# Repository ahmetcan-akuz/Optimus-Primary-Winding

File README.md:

# Optimus-Primary-Winding
This is the EE 464 Hardware Project Repository of Optimus Primary Winding

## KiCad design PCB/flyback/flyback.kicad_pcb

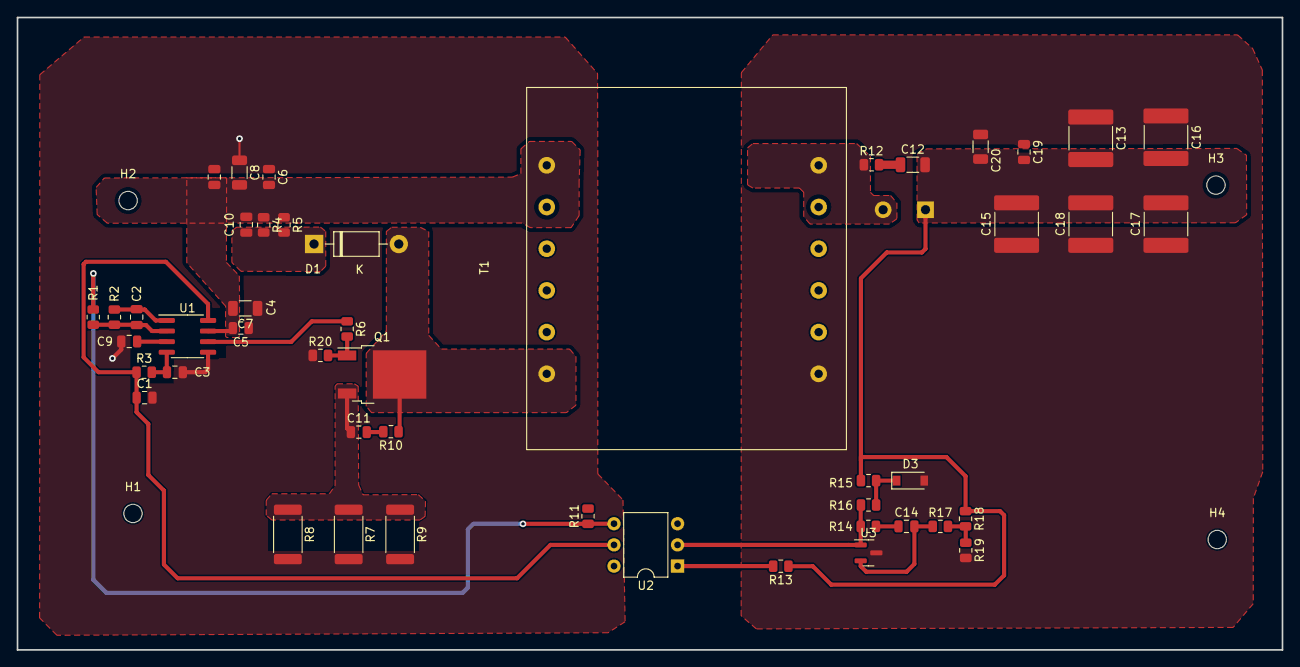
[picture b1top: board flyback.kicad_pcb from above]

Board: 2 copper layers, 151.7 x 75.8 mm, 52 parts (1 on the bottom side), 24 nets.

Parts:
C1, C4: 1u; C_0805_2012Metric
C2: 100p; C_0805_2012Metric
C3: 2.2n; C_0805_2012Metric
C5, C6, C19: 100n; C_0805_2012Metric
C7, C8, C20: 10n; C_1206_3216Metric
C9: 0.47n; C_0805_2012Metric
C10: 220n; C_0805_2012Metric
C11: 4.7n; C_0805_2012Metric
C12: 470p; C_1206_3216Metric
C13, C15, C16, C17: 10u; C_2220_5650Metric
C14: 1n; C_0805_2012Metric
C18: 4.7u; C_2220_5650Metric
D1: 1N4002; D_DO-41_SOD81_P10.16mm_Horizontal
D2: MBR10150; TO-220-2_Vertical
D3: MMSZ4713; D_SOD-123
H1, H2, H3, H4: MountingHole_Pad; MountingHole_2.2mm_M2
Q1: IRFR3410TRLPBF; TO-252-2
R1: 4.7k; R_0805_2012Metric
R2, R13, R15: 22k; R_0805_2012Metric
R3: 12k; R_0805_2012Metric
R4, R5, R16: 1k; R_0805_2012Metric
R6: 10; R_0805_2012Metric
R7, R8, R9: 150m; R_2512_6332Metric
R10: 47; R_0805_2012Metric
R11, R17, R19, R20: 10k; R_0805_2012Metric
R12: 100; R_0805_2012Metric
R14: 820k; R_0805_2012Metric
R18: 182k; R_0805_2012Metric
T1: Transformer_1P_1S; Transformer_37x44
U1: UC3843_SOIC8; SOIC-8_3.9x4.9mm_P1.27mm
U2: 4N25; DIP-6_W7.62mm
U3: TL431DBZ; SOT-23

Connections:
/Vfb: R1.1, R11.1, U2.4
/Vin: C4.2, C5.2, C6.2, C7.2, C8.2, C10.1, R4.1, R5.1, T1.6 (AA), U1.7 (VCC)
/Vout: C12.2, C13.2, C15.2, C16.2, C17.2, C18.2, C19.2, C20.2, D2.1 (K), R13.1, R15.1, R18.1
/Vref: C1.1, R3.1, U1.8 (VREF), U2.5
GND1: C1.2, C3.2, C4.1, C5.1, C6.1, C7.1, C8.1, C9.1, R7.2, R8.2, R9.2, R20.1, U1.5 (GND)
GND2: C13.1, C15.1, C16.1, C17.1, C18.1, C19.1, C20.1, D3.2 (A), R19.2, T1.12 (SA), U3.3 (A)
unnamed: C2.1, R1.2, R2.1, U1.2 (FB)
unnamed: C2.2, R2.2, U1.1 (COMP)
unnamed: C3.1, R3.2, U1.4 (RC)
unnamed: C9.2, U1.3 (CS)
unnamed: C10.2, D1.1 (K), R4.2, R5.2
unnamed: C11.1, Q1.3 (S), R7.1, R8.1, R9.1
unnamed: C11.2, R10.2
unnamed: C12.1, R12.2
unnamed: C14.1, R14.2
unnamed: C14.2, R17.1, U3.2 (REF)
unnamed: D1.2 (A), Q1.2 (D), R10.1, T1.1 (AB)
unnamed: D2.2 (A), R12.1, T1.7 (SB)
unnamed: D3.1 (K), R15.2, R16.1
unnamed: Q1.1 (G), R6.2, R20.2
unnamed: R6.1, U1.6 (OUT)
unnamed: R13.2, U2.1
unnamed: R14.1, R16.2, U2.2, U3.1 (K)
unnamed: R17.2, R18.2, R19.1

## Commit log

2023-04-15 Initial simulation+ tl431 files
2023-04-27 Transformer Design Calculator Excel was added.
2023-04-28 Magnetic Design Excel Updated Source Documents Added
2023-04-28 Magnetic Design Updated
2023-04-28 Magnetic Design Update
    Design was updated as 8uH/0.6 duty cycle version.
2023-05-02 Magnetic Design Updated wrt CCM Mode
2023-05-02 Magnetic Desing Update
    Excel was updated. Datasheet of core was added.
2023-05-02 Cable Selection Part was added.
2023-05-03 Magnetic Design Updated
    Datasheet of core also added to repo.
2023-05-03 Cable resistances were added
2023-05-03 Updated the simulation file with the non-idealities
    Component list file added
    Simulation file added with magnetic design and non-idealities
2023-05-04 Component List Update
2023-05-04 Neat looking simulation file
    Adjusted some parameters of the controller
2023-05-04 Duty Cycle, Topology Discussion
2023-05-04 update on components and sim file
2023-05-04 Magnetic Design Parameters were finalized
2023-05-05 Magnetic Design Report Update
2023-05-05 Simulations and Design Decisions
2023-05-05 Magnetic Design Report Updated
2023-05-05 Indtroduction and cover part added
2023-05-05 Simulation Report Finalized
2023-05-05 PDF of Simulation Report
2023-05-06 update on components and simulation
2023-05-06 Updates on component list simulation
2023-05-09 Presentation for simulations and thermal design
2023-05-10 Update on Excel of MD
2023-05-10 Presentation added, Excel Updated
2023-05-10 Presentation Finalized
2023-05-10 Temp Rise Calculation Added
2023-05-10 Presentation Updated
2023-05-13 FLyback_Simplified_Version
2023-05-16 Simplified Design Update
    Additional RC circuit eliminated. Snubber design updated.
2023-05-17 RCD Snubber Updated
2023-05-17 Flyback Design Excel Added
2023-05-17 update on schematics
2023-05-17 update on components
2023-05-17 PCB Design Added
2023-05-18 Schematic Update
2023-05-22 Flyback Update
2023-05-22 Schematic Finalize
2023-05-23 PCB Update
2023-05-23 Layout Update
2023-05-29 Gerber Files Added
2023-05-29 Transformer Footprint Updated
2023-06-01 imported kicad files to altium-baris
2023-06-02 Lib1
2023-06-02 Lib2
2023-06-02 Lib3
2023-06-02 Lib4
2023-06-02 Lib5
2023-06-02 Lib6
2023-06-02 footprint1
2023-06-02 footprint3
2023-06-02 test
2023-06-02 footprint5
2023-06-02 foortprint_last
2023-06-14 V3_flyback
2023-06-14 asca
2023-06-16 Non ideal diodes added to simulation
2023-06-24 Sim report moved
2023-06-24 move
2023-06-24 Final Project report added
2023-06-24 Report Update
2023-06-24 lt spice
2023-06-24 Magnetic Design Added
2023-06-28 Last Configuration
